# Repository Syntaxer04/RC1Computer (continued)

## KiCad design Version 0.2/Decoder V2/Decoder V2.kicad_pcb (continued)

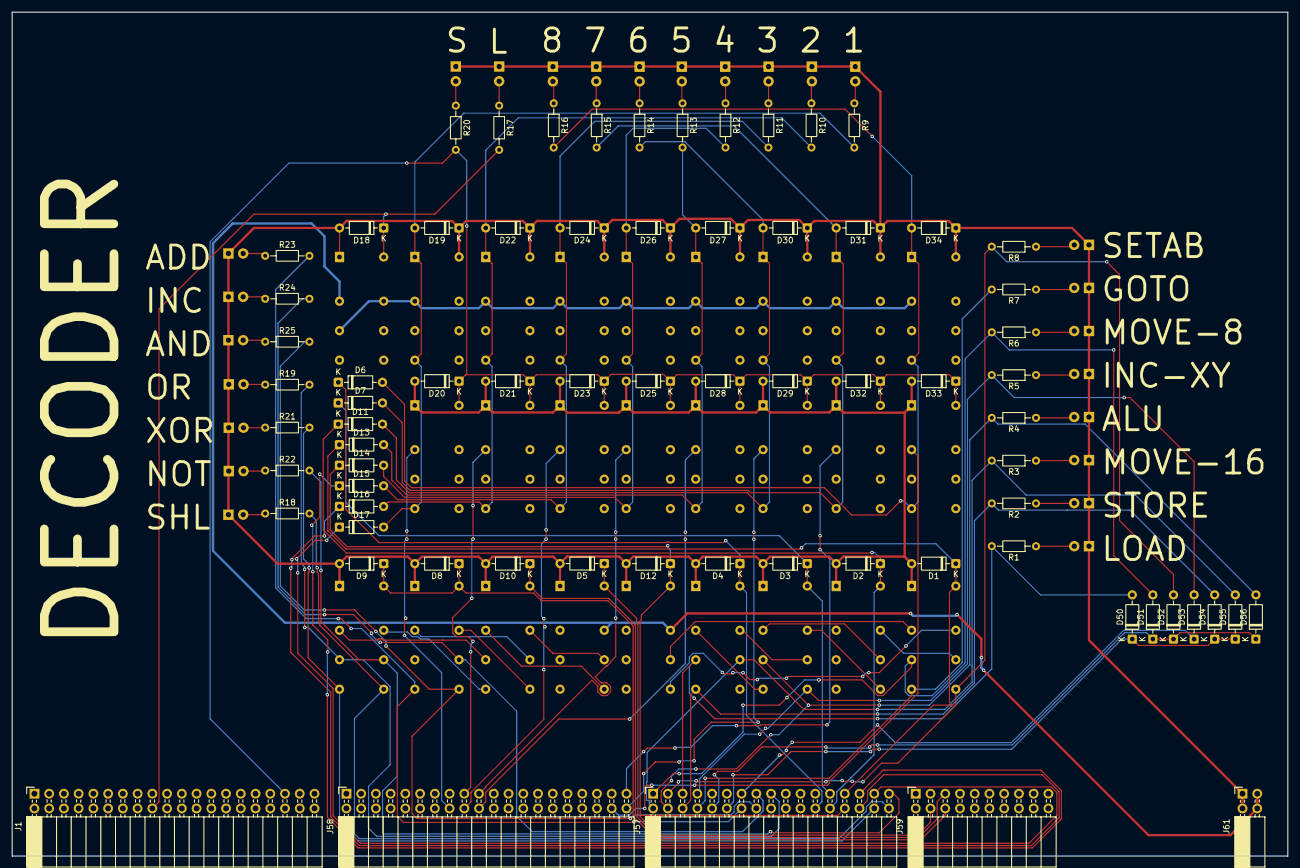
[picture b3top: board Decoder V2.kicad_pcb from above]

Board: 2 copper layers, 219.8 x 145.4 mm, 122 parts (0 on the bottom side), 88 nets.

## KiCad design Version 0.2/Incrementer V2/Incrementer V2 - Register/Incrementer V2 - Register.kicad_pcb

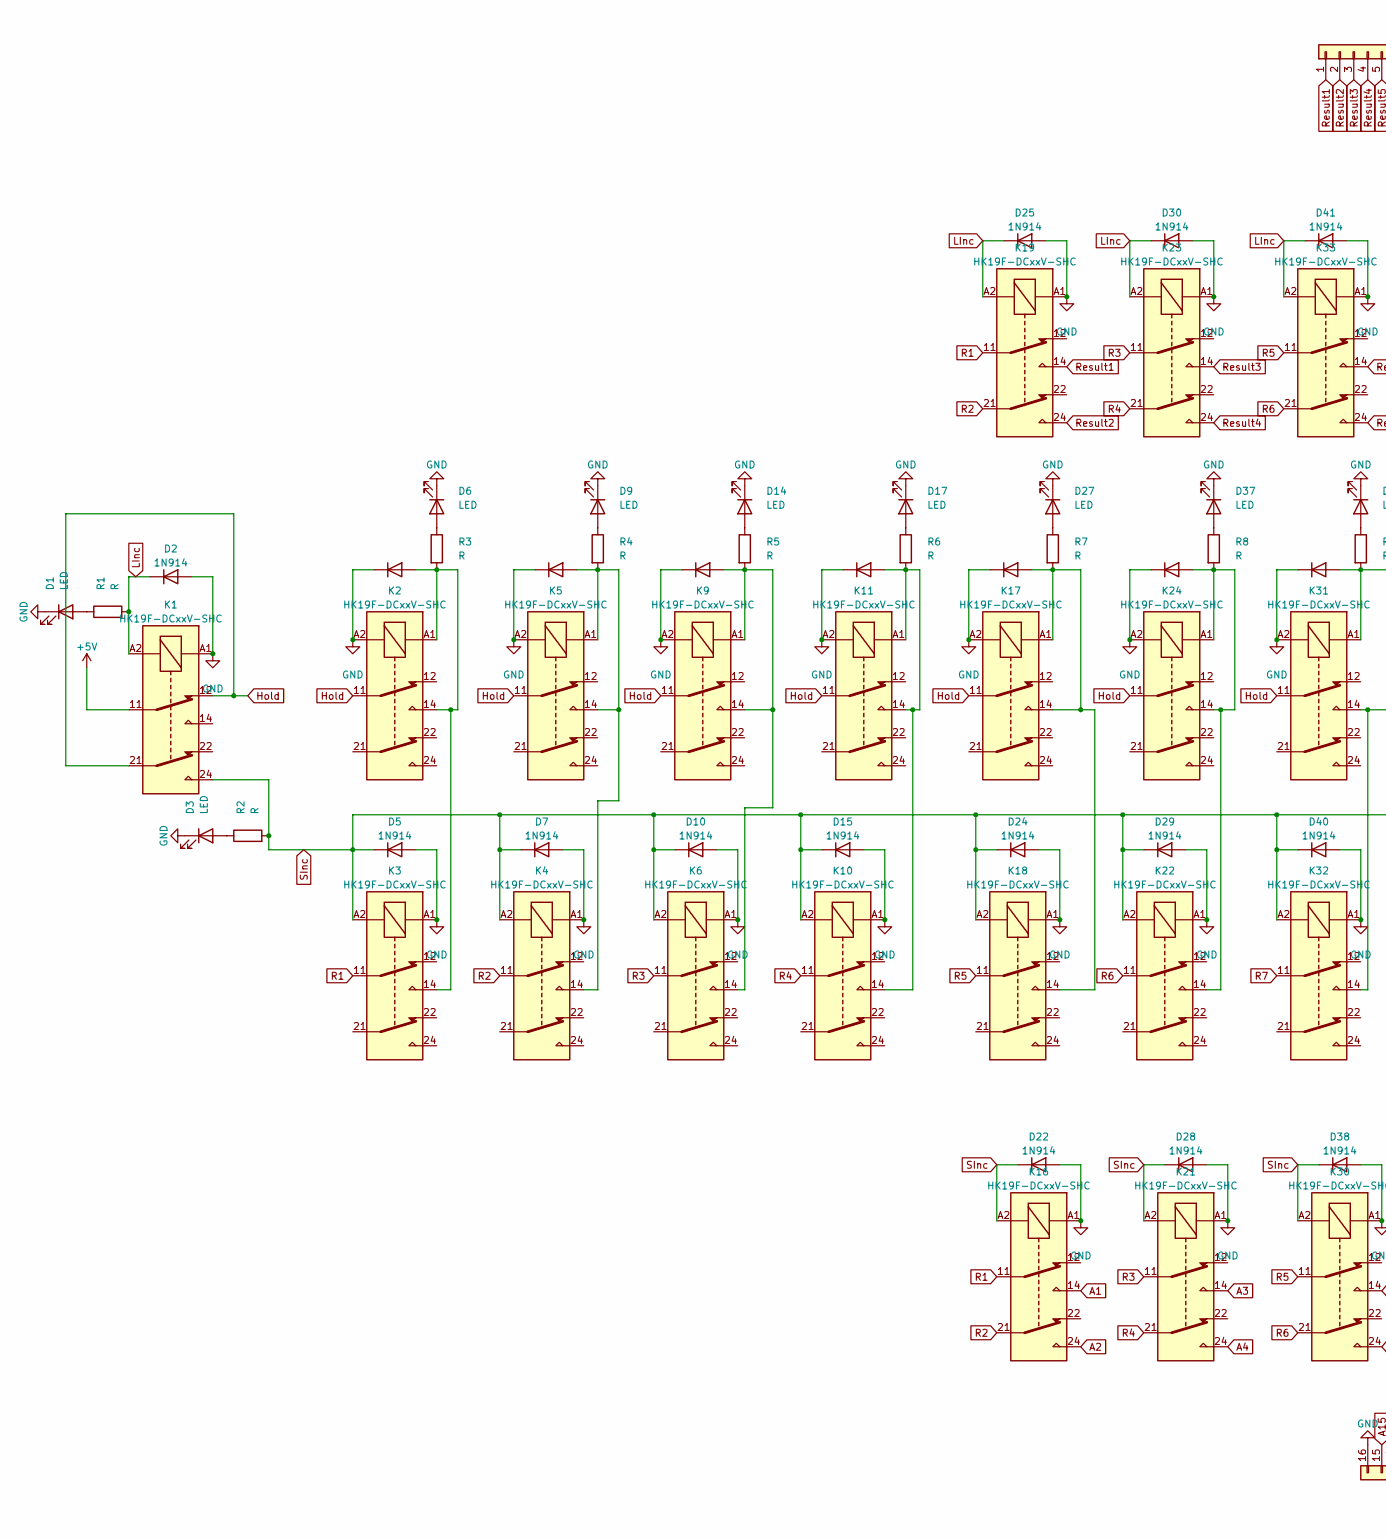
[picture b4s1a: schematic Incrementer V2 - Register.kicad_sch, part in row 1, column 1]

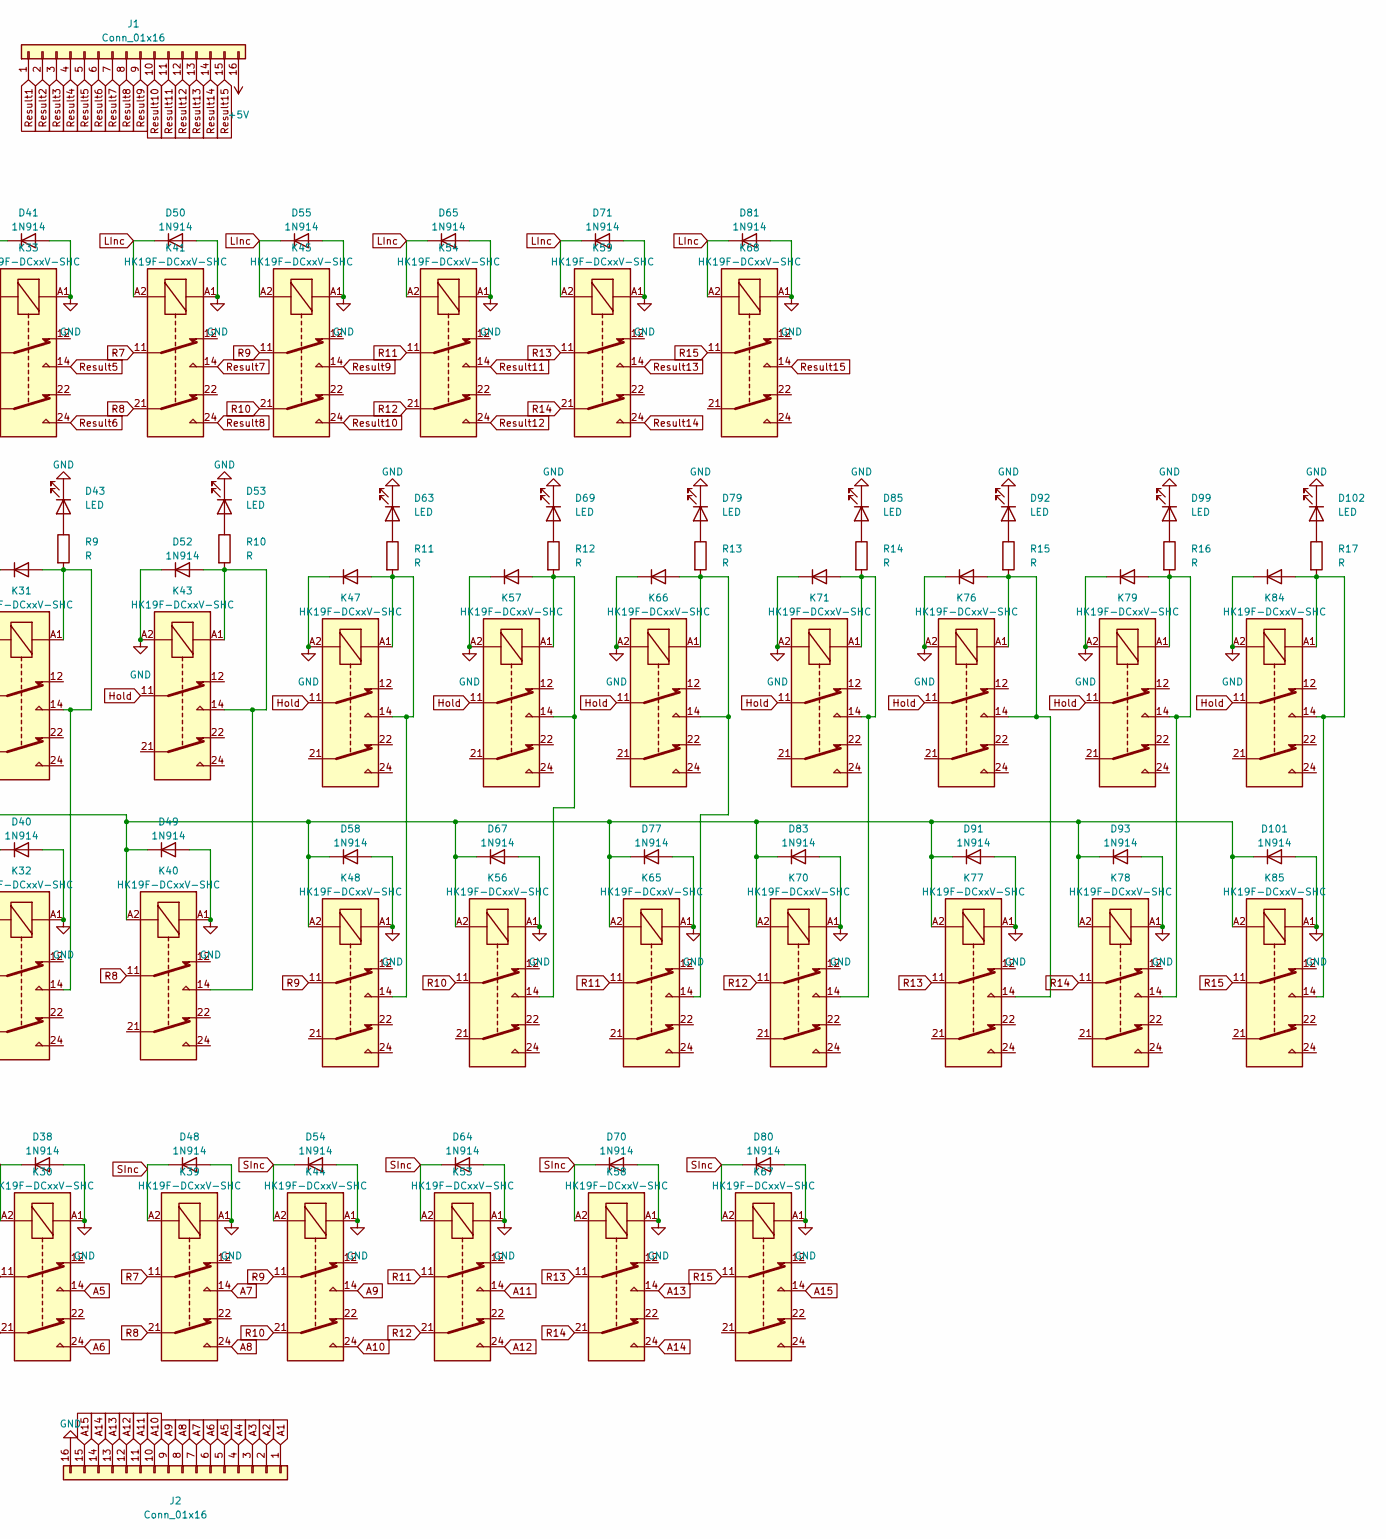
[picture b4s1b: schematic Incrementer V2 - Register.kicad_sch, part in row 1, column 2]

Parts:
D1, D3, D6, D9, D14, D17, D27, D37, D43, D53, D63, D69, D79, D85, D92, D99, D102: LED; LED_D5.0mm ohne SilkS
D2, D4, D5, D7, D8, D10, D13, D15, D16, D22, D23, D24, D25, D28, D29, D30, D31, D38, D39, D40, D41, D48, D49, D50, D52, D54, D55, D57, D58, D64, D65, D67, D68, D70, D71, D77, D78, D80, D81, D83, D84, D90, D91, D93, D94, D100, D101: 1N914; D_DO-35_SOD27_P7.62mm_Horizontal
J1, J2: Conn_01x16; PinHeader_1x16_P2.54mm_Vertical
K1, K2, K3, K4, K5, K6, K9, K10, K11, K16, K17, K18, K19, K21, K22, K23, K24, K30, K31, K32, K33, K39, K40, K41, K43, K44, K45, K47, K48, K53, K54, K56, K57, K58, K59, K65, K66, K67, K68, K70, K71, K76, K77, K78, K79, K84, K85: HK19F-DCxxV-SHC; Relay_DPDT_Finder_30.22 ohne SilkS
R1, R2, R3, R4, R5, R6, R7, R8, R9, R10, R11, R12, R13, R14, R15, R16, R17: R; R_Axial_DIN0204_L3.6mm_D1.6mm_P7.62mm_Horizontal

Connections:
+5V: J1.16, K1.11
A1: J2.1, K16.14
A2: J2.2, K16.24
A3: J2.3, K21.14
A4: J2.4, K21.24
A5: J2.5, K30.14
A6: J2.6, K30.24
A7: J2.7, K39.14
A8: J2.8, K39.24
A9: J2.9, K44.14
A10: J2.10, K44.24
A11: J2.11, K53.14
A12: J2.12, K53.24
A13: J2.13, K58.14
A14: J2.14, K58.24
A15: J2.15, K67.14
GND: D1.1 (K), D2.2 (A), D3.1 (K), D4.1 (K), D5.2 (A), D6.1 (K), D7.2 (A), D8.1 (K), D9.1 (K), D10.2 (A), D13.1 (K), D14.1 (K), D15.2 (A), D16.1 (K), D17.1 (K), D22.2 (A), D23.1 (K), D24.2 (A), D25.2 (A), D27.1 (K), D28.2 (A), D29.2 (A), D30.2 (A), D31.1 (K), D37.1 (K), D38.2 (A), D39.1 (K), D40.2 (A), D41.2 (A), D43.1 (K), D48.2 (A), D49.2 (A), D50.2 (A), D52.1 (K), D53.1 (K), D54.2 (A), D55.2 (A), D57.1 (K), D58.2 (A), D63.1 (K), D64.2 (A), D65.2 (A), D67.2 (A), D68.1 (K), D69.1 (K), D70.2 (A), D71.2 (A), D77.2 (A), D78.1 (K), D79.1 (K), D80.2 (A), D81.2 (A), D83.2 (A), D84.1 (K), D85.1 (K), D90.1 (K), D91.2 (A), D92.1 (K), D93.2 (A), D94.1 (K), D99.1 (K), D100.1 (K), D101.2 (A), D102.1 (K), J2.16, K1.A1, K2.A2, K3.A1, K4.A1, K5.A2, K6.A1, K9.A2, K10.A1, K11.A2, K16.A1, K17.A2, K18.A1, K19.A1, K21.A1, K22.A1, K23.A1, K24.A2, K30.A1, K31.A2, K32.A1, K33.A1, K39.A1, K40.A1, K41.A1, K43.A2, K44.A1, K45.A1, K47.A2, K48.A1, K53.A1, K54.A1, K56.A1, K57.A2, K58.A1, K59.A1, K65.A1, K66.A2, K67.A1, K68.A1, K70.A1, K71.A2, K76.A2, K77.A1, K78.A1, K79.A2, K84.A2, K85.A1
Hold: K1.12, K1.21, K2.11, K5.11, K9.11, K11.11, K17.11, K24.11, K31.11, K43.11, K47.11, K57.11, K66.11, K71.11, K76.11, K79.11, K84.11
LInc: D2.1 (K), D25.1 (K), D30.1 (K), D41.1 (K), D50.1 (K), D55.1 (K), D65.1 (K), D71.1 (K), D81.1 (K), K1.A2, K19.A2, K23.A2, K33.A2, K41.A2, K45.A2, K54.A2, K59.A2, K68.A2, R1.2
unnamed: D1.2 (A), R1.1
unnamed: D3.2 (A), R2.1
unnamed: D4.2 (A), K2.14, K2.A1, K3.14, R3.2
unnamed: D6.2 (A), R3.1
unnamed: D8.2 (A), K4.14, K5.14, K5.A1, R4.2
unnamed: D9.2 (A), R4.1
unnamed: D13.2 (A), K6.14, K9.14, K9.A1, R5.2
unnamed: D14.2 (A), R5.1
unnamed: D16.2 (A), K10.14, K11.14, K11.A1, R6.2
unnamed: D17.2 (A), R6.1
unnamed: D23.2 (A), K17.14, K17.A1, K18.14, R7.2
unnamed: D27.2 (A), R7.1
unnamed: D31.2 (A), K22.14, K24.14, K24.A1, R8.2
unnamed: D37.2 (A), R8.1
unnamed: D39.2 (A), K31.14, K31.A1, K32.14, R9.2
unnamed: D43.2 (A), R9.1
unnamed: D52.2 (A), K40.14, K43.14, K43.A1, R10.2
unnamed: D53.2 (A), R10.1
unnamed: D57.2 (A), K47.14, K47.A1, K48.14, R11.2
unnamed: D63.2 (A), R11.1
unnamed: D68.2 (A), K56.14, K57.14, K57.A1, R12.2
unnamed: D69.2 (A), R12.1
unnamed: D78.2 (A), K65.14, K66.14, K66.A1, R13.2
unnamed: D79.2 (A), R13.1
unnamed: D84.2 (A), K70.14, K71.14, K71.A1, R14.2
unnamed: D85.2 (A), R14.1
unnamed: D90.2 (A), K76.14, K76.A1, K77.14, R15.2
unnamed: D92.2 (A), R15.1
unnamed: D94.2 (A), K78.14, K79.14, K79.A1, R16.2
unnamed: D99.2 (A), R16.1
unnamed: D100.2 (A), K84.14, K84.A1, K85.14, R17.2
unnamed: D102.2 (A), R17.1
R1: K3.11, K16.11, K19.11
R2: K4.11, K16.21, K19.21
R3: K6.11, K21.11, K23.11
R4: K10.11, K21.21, K23.21
R5: K18.11, K30.11, K33.11
R6: K22.11, K30.21, K33.21
R7: K32.11, K39.11, K41.11
R8: K39.21, K40.11, K41.21
R9: K44.11, K45.11, K48.11
R10: K44.21, K45.21, K56.11
R11: K53.11, K54.11, K65.11
R12: K53.21, K54.21, K70.11
R13: K58.11, K59.11, K77.11
R14: K58.21, K59.21, K78.11
R15: K67.11, K68.11, K85.11
Result1: J1.1, K19.14
Result2: J1.2, K19.24
Result3: J1.3, K23.14
Result4: J1.4, K23.24
Result5: J1.5, K33.14
Result6: J1.6, K33.24
Result7: J1.7, K41.14
Result8: J1.8, K41.24
Result9: J1.9, K45.14
Result10: J1.10, K45.24
Result11: J1.11, K54.14
Result12: J1.12, K54.24
Result13: J1.13, K59.14
Result14: J1.14, K59.24
Result15: J1.15, K68.14
SInc: D5.1 (K), D7.1 (K), D10.1 (K), D15.1 (K), D22.1 (K), D24.1 (K), D28.1 (K), D29.1 (K), D38.1 (K), D40.1 (K), D48.1 (K), D49.1 (K), D54.1 (K), D58.1 (K), D64.1 (K), D67.1 (K), D70.1 (K), D77.1 (K), D80.1 (K), D83.1 (K), D91.1 (K), D93.1 (K), D101.1 (K), K1.24, K3.A2, K4.A2, K6.A2, K10.A2, K16.A2, K18.A2, K21.A2, K22.A2, K30.A2, K32.A2, K39.A2, K40.A2, K44.A2, K48.A2, K53.A2, K56.A2, K58.A2, K65.A2, K67.A2, K70.A2, K77.A2, K78.A2, K85.A2, R2.2

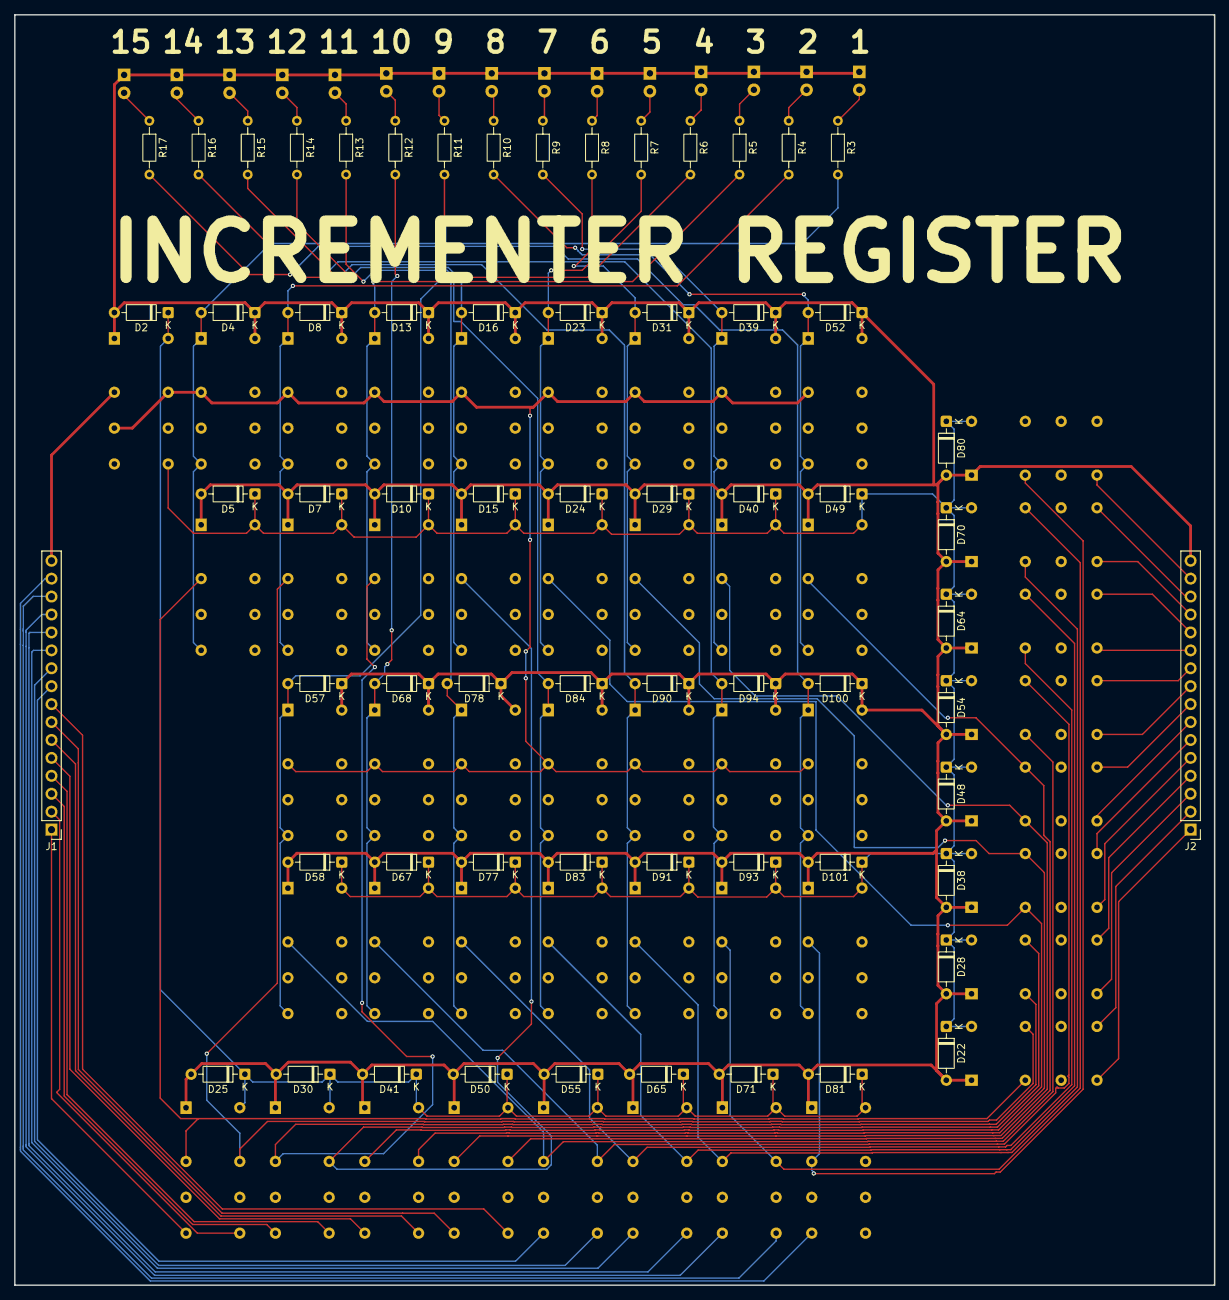
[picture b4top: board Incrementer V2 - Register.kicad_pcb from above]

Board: 2 copper layers, 170.0 x 180.0 mm, 126 parts (0 on the bottom side), 80 nets.

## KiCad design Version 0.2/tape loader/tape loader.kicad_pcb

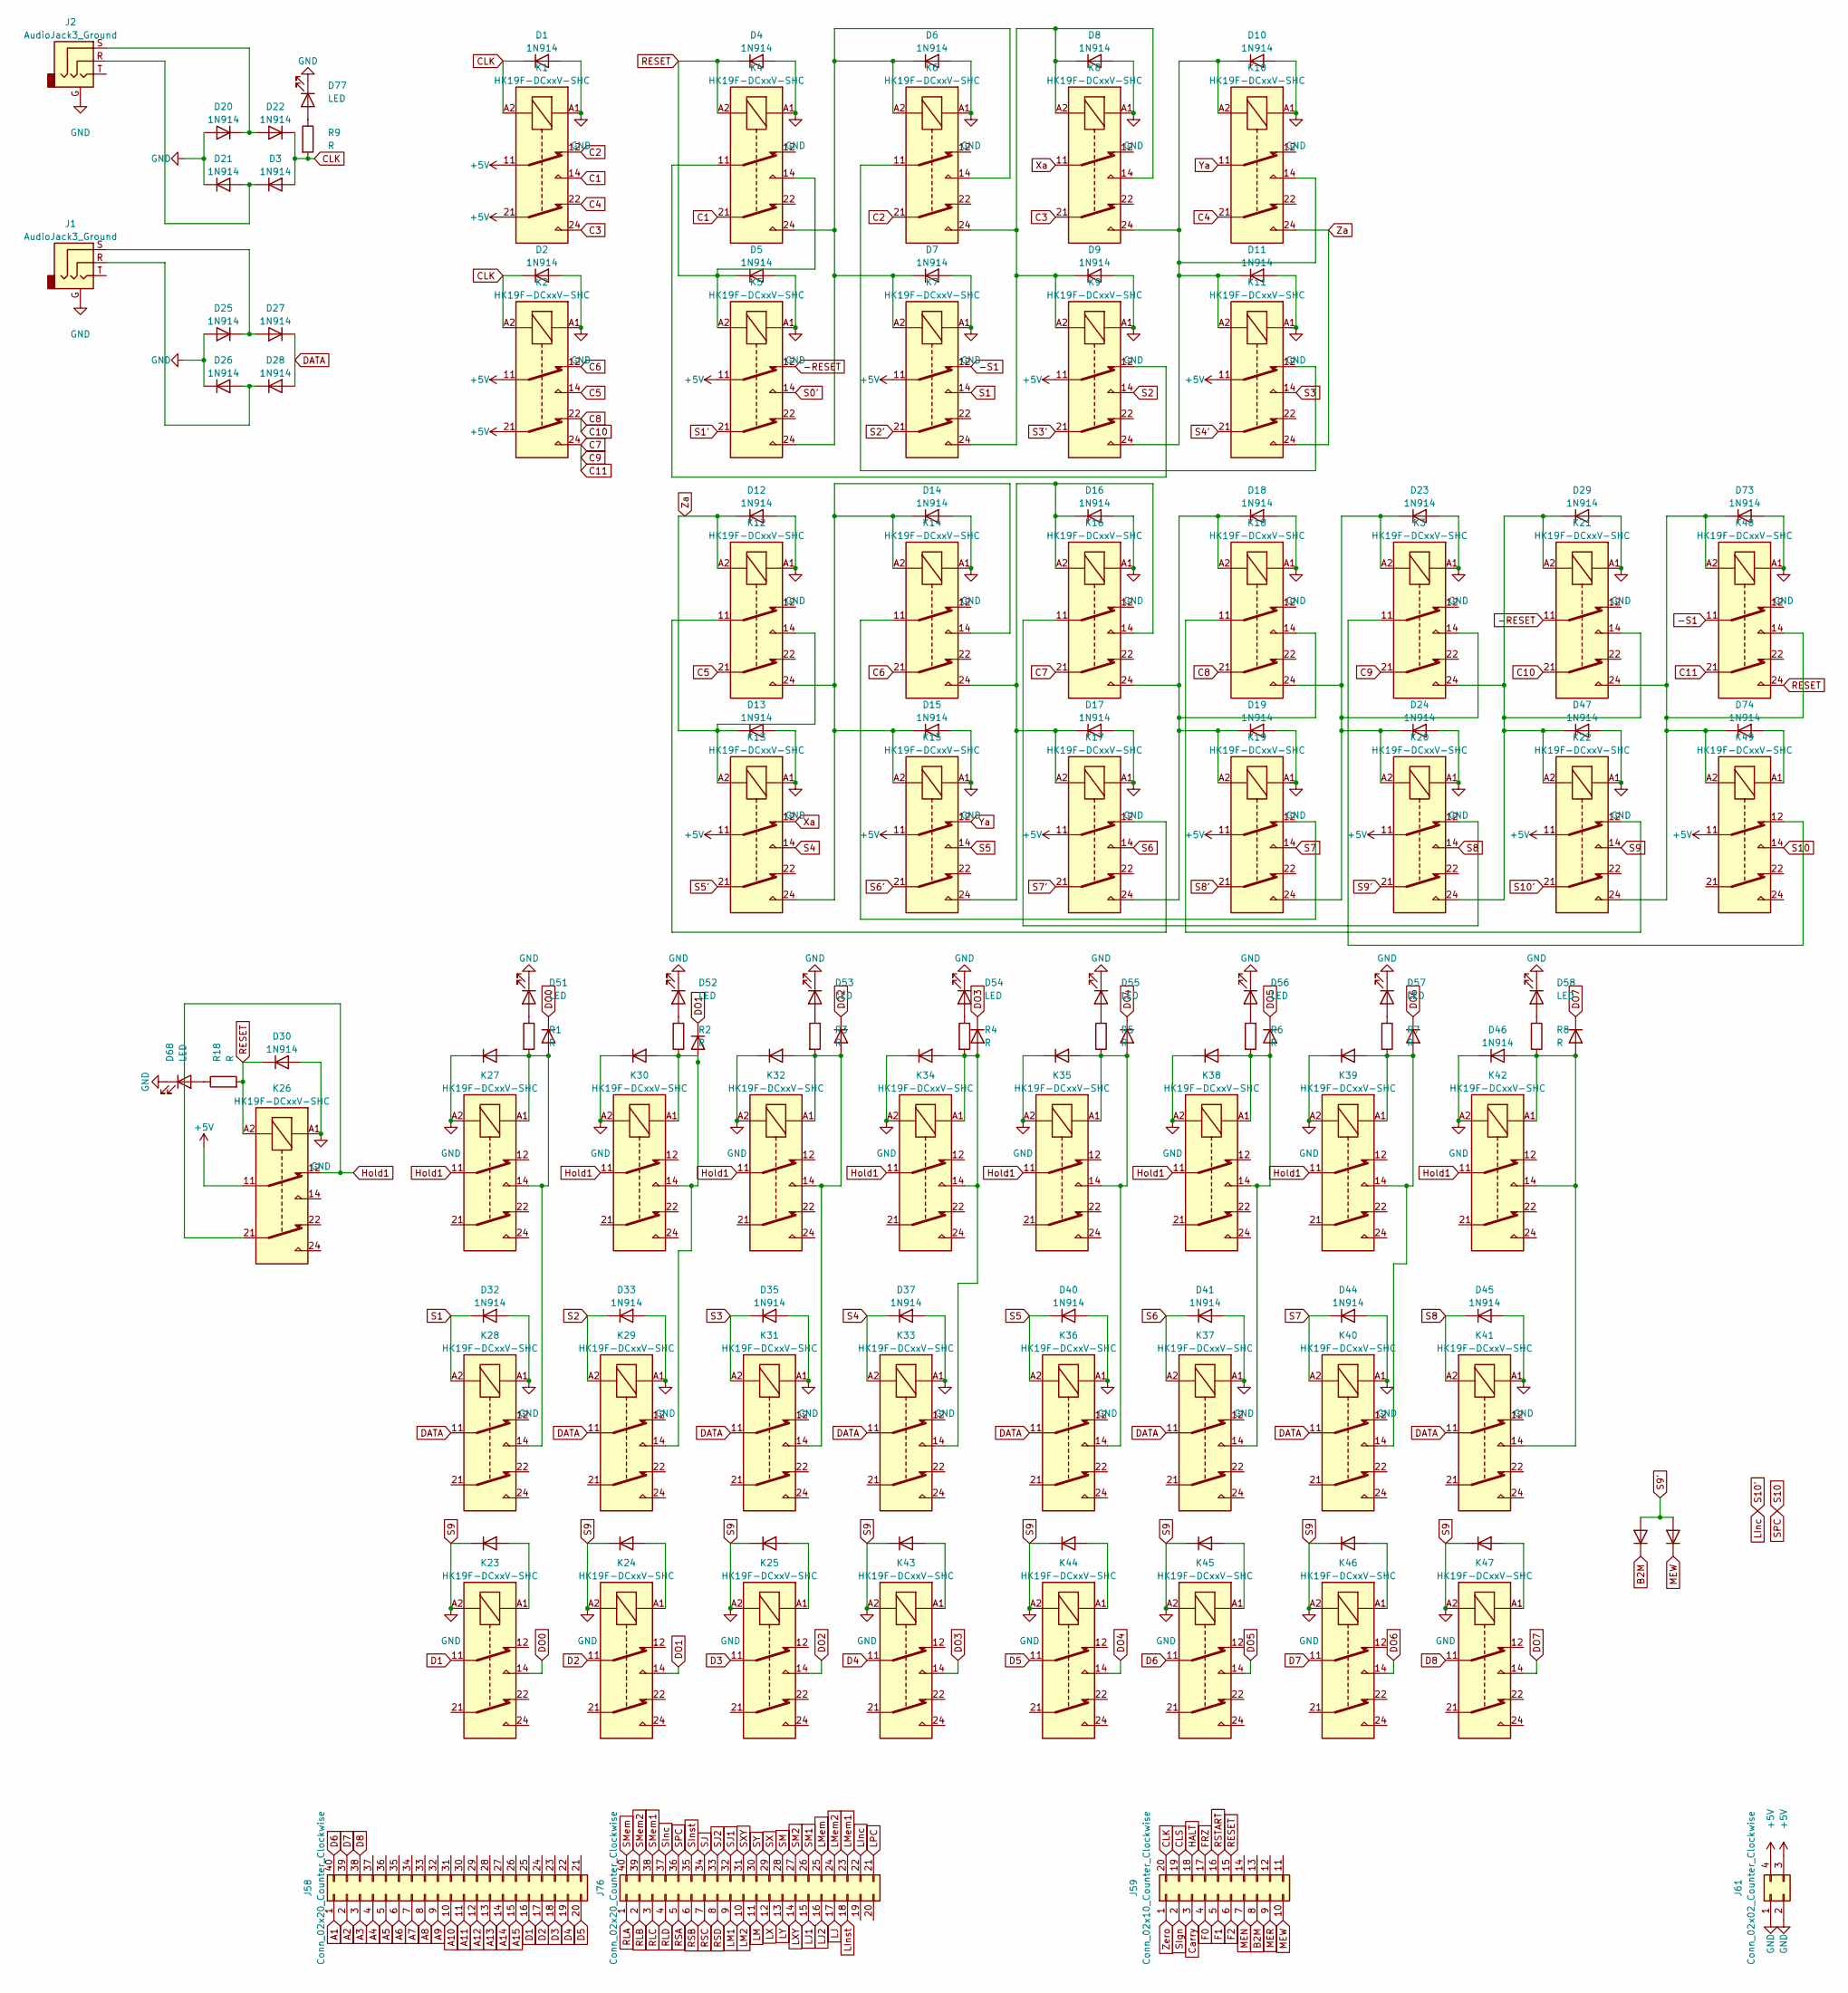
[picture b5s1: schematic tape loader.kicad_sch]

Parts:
D1, D2, D3, D4, D5, D6, D7, D8, D9, D10, D11, D12, D13, D14, D15, D16, D17, D18, D19, D20, D21, D22, D23, D24, D25, D26, D27, D28, D29, D30, D31, D32, D33, D34, D35, D36, D37, D38, D39, D40, D41, D42, D43, D44, D45, D46, D47, D48, D49, D50, D59, D60, D61, D62, D63, D64, D65, D66, D67, D69, D70, D71, D72, D73, D74, D75, D76: 1N914; D_DO-35_SOD27_P7.62mm_Horizontal
D51, D52, D53, D54, D55, D56, D57, D58, D68, D77: LED; LED_D5.0mm ohne SilkS
J1, J2: AudioJack3_Ground; Jack_3.5mm_PJ320E_Horizontal
J58, J76: Conn_02x20_Counter_Clockwise; PinSocket_2x20_P2.54mm_Horizontal
J59: Conn_02x10_Counter_Clockwise; PinSocket_2x10_P2.54mm_Horizontal
J61: Conn_02x02_Counter_Clockwise; PinSocket_2x02_P2.54mm_Horizontal
K1, K2, K3, K4, K5, K6, K7, K8, K9, K10, K11, K12, K13, K14, K15, K16, K17, K18, K19, K20, K21, K22, K23, K24, K25, K26, K27, K28, K29, K30, K31, K32, K33, K34, K35, K36, K37, K38, K39, K40, K41, K42, K43, K44, K45, K46, K47, K48, K49: HK19F-DCxxV-SHC; Relay_DPDT_Finder_30.22 ohne SilkS
R1, R2, R3, R4, R5, R6, R7, R8, R9, R18: R; R_Axial_DIN0204_L3.6mm_D1.6mm_P7.62mm_Horizontal

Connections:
+5V: J61.3, J61.4, K1.11, K1.21, K2.11, K2.21, K5.11, K7.11, K9.11, K11.11, K13.11, K15.11, K17.11, K19.11, K20.11, K22.11, K26.11, K49.11
-RESET: K5.12, K21.11
-S1: K7.12, K48.11
A1: J58.1
A2: J58.2
A3: J58.3
A4: J58.4
A5: J58.5
A6: J58.6
A7: J58.7
A8: J58.8
A9: J58.9
A10: J58.10
A11: J58.11
A12: J58.12
A13: J58.13
A14: J58.14
A15: J58.15
B2M: D75.1 (K), J59.8
C1: K1.14, K4.21
C2: K1.12, K6.21
C3: K1.24, K8.21
C4: K1.22, K10.21
C5: K2.14, K12.21
C6: K2.12, K14.21
C10: K2.22, K18.21, K21.21
C11: K2.24, K3.21, K16.21, K48.21
CLK: D1.1 (K), D2.1 (K), D3.2 (A), D22.1 (K), J59.20, K1.A2, K2.A2, R9.2
CLS: J59.19
Carry: J59.3
D1: J58.16, K23.11
D2: J58.17, K24.11
D3: J58.18, K25.11
D4: J58.19, K43.11
D5: J58.20, K44.11
D6: J58.40, K45.11
D7: J58.39, K46.11
D8: J58.38, K47.11
DATA: D27.1 (K), D28.2 (A), K28.11, K29.11, K31.11, K33.11, K36.11, K37.11, K40.11, K41.11
DO0: D48.1 (K), K23.14
DO1: D49.1 (K), K24.14
DO2: D50.1 (K), K25.14
DO3: D59.1 (K), K43.14
DO4: D60.1 (K), K44.14
DO5: D61.1 (K), K45.14
DO6: D62.1 (K), K46.14
DO7: D63.1 (K), K47.14
F0: J59.4
F1: J59.5
F2: J59.6
FRZ: J59.17
HALT: J59.18
Hold1: K26.12, K26.21, K27.11, K30.11, K32.11, K34.11, K35.11, K38.11, K39.11, K42.11
LInc: J76.22, K22.21
LInst: J76.18
LJ1: J76.15
LJ2: J76.16
LJ: J76.17
LM: J76.11
LM1: J76.9
LM2: J76.10
LMem: J76.25
LMem1: J76.23
LMem2: J76.24
LPC: J76.21
LX: J76.12
LXY: J76.14
LY: J76.13
MEN: J59.7
MER: J59.9
MEW: D76.1 (K), J59.10
unnamed: D6.1 (K), D7.1 (K), K4.24, K5.24, K6.14, K6.A2, K7.A2
unnamed: D8.1 (K), D9.1 (K), K6.24, K7.24, K8.14, K8.A2, K9.A2
unnamed: D10.1 (K), D11.1 (K), K8.24, K9.24, K10.14, K10.A2, K11.A2
unnamed: D14.1 (K), D15.1 (K), K12.24, K13.24, K14.14, K14.A2, K15.A2
unnamed: D16.1 (K), D17.1 (K), K14.24, K15.24, K16.14, K16.A2, K17.A2
unnamed: D18.1 (K), D19.1 (K), K16.24, K17.24, K18.14, K18.A2, K19.A2
unnamed: D20.1 (K), D22.2 (A), J2.S
unnamed: D3.1 (K), D21.2 (A), J2.R
unnamed: D23.1 (K), D24.1 (K), K3.14, K3.A2, K18.24, K19.24, K20.A2
unnamed: D25.1 (K), D27.2 (A), J1.S
unnamed: D26.2 (A), D28.1 (K), J1.R
unnamed: D29.1 (K), D47.1 (K), K3.24, K20.24, K21.14, K21.A2, K22.A2
unnamed: D31.2 (A), D48.2 (A), K27.14, K27.A1, K28.14, R1.2
unnamed: D34.2 (A), D49.2 (A), K29.14, K30.14, K30.A1, R2.2
unnamed: D36.2 (A), D50.2 (A), K31.14, K32.14, K32.A1, R3.2
unnamed: D38.2 (A), D59.2 (A), K33.14, K34.14, K34.A1, R4.2
unnamed: D39.2 (A), D60.2 (A), K35.14, K35.A1, K36.14, R5.2
unnamed: D42.2 (A), D61.2 (A), K37.14, K38.14, K38.A1, R6.2
unnamed: D43.2 (A), D62.2 (A), K39.14, K39.A1, K40.14, R7.2
unnamed: D46.2 (A), D63.2 (A), K41.14, K42.14, K42.A1, R8.2
unnamed: D51.2 (A), R1.1
unnamed: D52.2 (A), R2.1
unnamed: D53.2 (A), R3.1
unnamed: D54.2 (A), R4.1
unnamed: D55.2 (A), R5.1
unnamed: D56.2 (A), R6.1
unnamed: D57.2 (A), R7.1
unnamed: D58.2 (A), R8.1
unnamed: D64.2 (A), K23.A1
unnamed: D65.2 (A), K24.A1
unnamed: D66.2 (A), K25.A1
unnamed: D67.2 (A), K43.A1
unnamed: D68.2 (A), R18.1
unnamed: D69.2 (A), K44.A1
unnamed: D70.2 (A), K45.A1
unnamed: D71.2 (A), K46.A1
unnamed: D72.2 (A), K47.A1
unnamed: D73.1 (K), D74.1 (K), K21.24, K22.24, K48.14, K48.A2, K49.A2
unnamed: D74.2 (A), K49.A1
unnamed: D77.2 (A), R9.1
unnamed: K3.11, K49.12
unnamed: K4.11, K9.12
unnamed: K6.11, K11.12
unnamed: K12.11, K17.12
unnamed: K14.11, K19.12
unnamed: K16.11, K20.12
unnamed: K18.11, K22.12
RESET: D4.1 (K), D5.1 (K), D30.1 (K), J59.15, K4.14, K4.A2, K5.A2, K26.A2, K48.24, R18.2
RLA: J76.1
RLB: J76.2
RLC: J76.3
RLD: J76.4
RSA: J76.5
RSB: J76.6
RSC: J76.7
RSD: J76.8
RSTART: J59.16
S0': K5.14
S1: D32.1 (K), K7.14, K28.A2
S1': K5.21
S2: D33.1 (K), K9.14, K29.A2
S2': K7.21
S3: D35.1 (K), K11.14, K31.A2
S3': K9.21
S4: D37.1 (K), K13.14, K33.A2
S4': K11.21
S5': K13.21
S6: D41.1 (K), K17.14, K37.A2
S6': K15.21
S7: D44.1 (K), K19.14, K40.A2
S7': K17.21
S8: D45.1 (K), K20.14, K41.A2
S8': K19.21
S9': D75.2 (A), D76.2 (A), K20.21
SIgn: J59.2
SInst: J76.35
SJ1: J76.32
SJ2: J76.33
SJ: J76.34
SM: J76.28
SM1: J76.26
SM2: J76.27
SMem: J76.40
SMem1: J76.38
SMem2: J76.39
SX: J76.29
SXY: J76.31
SY: J76.30
Xa: K8.11, K13.12
Ya: K10.11, K15.12
Za: D12.1 (K), D13.1 (K), K10.24, K11.24, K12.14, K12.A2, K13.A2
Zero: J59.1

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
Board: 2 copper layers, 142 parts (0 on the bottom side), 95 nets, no tracks yet.
